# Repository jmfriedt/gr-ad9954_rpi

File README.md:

# gr-ad9954_rpi

Daughter board for the Raspberry Pi 3 or 4 fitted with an Analog Devices AD9954 Direct 
Digital Synthesizer.

KiCAD 6 schematic and board are provided.

Mechanical analysis using FreeCAD of the board compatibility with the RPi4:

The Python 3 script ``ad9954.py`` was used to demonstrate proper operation of the board:

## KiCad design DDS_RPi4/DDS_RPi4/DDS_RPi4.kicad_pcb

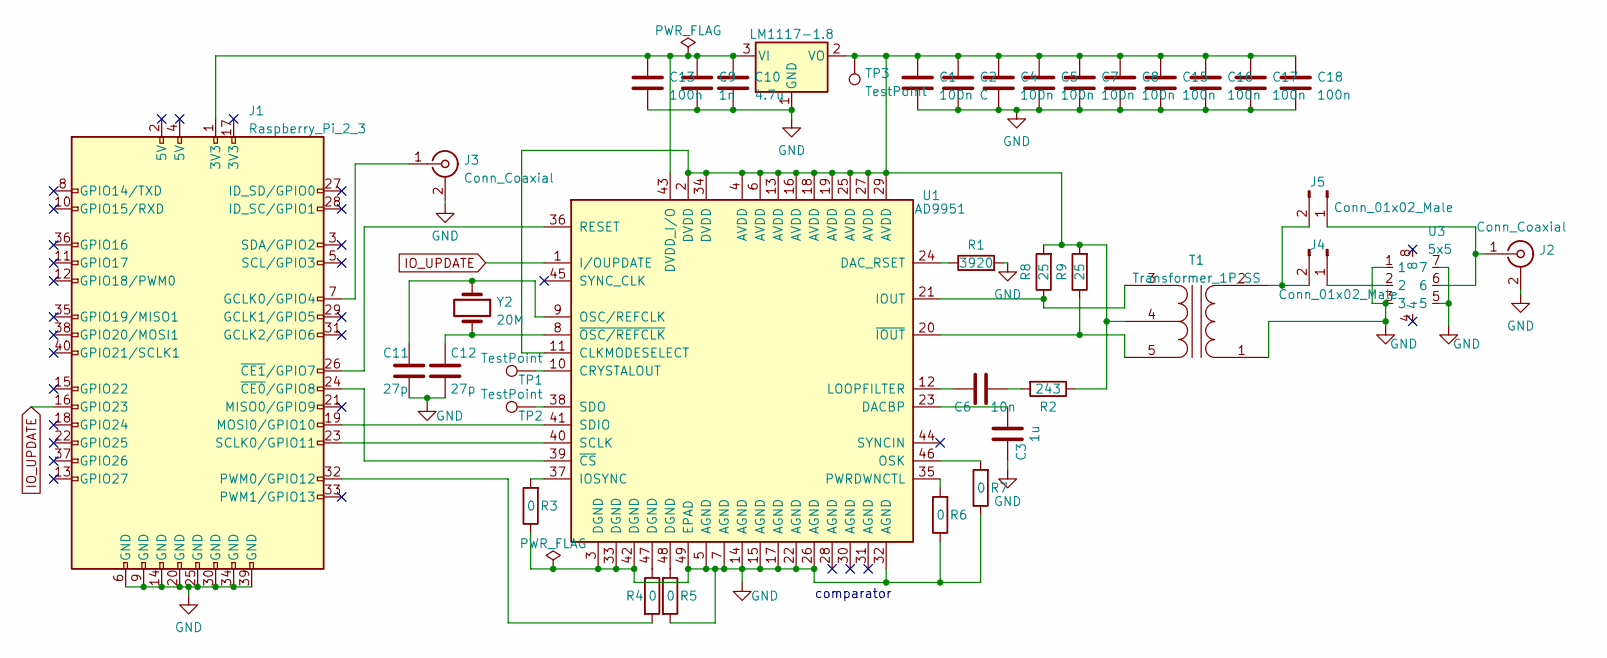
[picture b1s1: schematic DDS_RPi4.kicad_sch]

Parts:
C1, C4, C5, C7, C8, C13, C15, C16, C17, C18: 100n; C_0603_1608Metric_Pad1.08x0.95mm_HandSolder
C2: C; C_0603_1608Metric_Pad1.08x0.95mm_HandSolder
C3: 1u; C_0603_1608Metric_Pad1.08x0.95mm_HandSolder
C6: 10n; C_0603_1608Metric_Pad1.08x0.95mm_HandSolder
C9: 1n; C_0603_1608Metric_Pad1.08x0.95mm_HandSolder
C10: 4.7u; C_0603_1608Metric_Pad1.08x0.95mm_HandSolder
C11, C12: 27p; C_0603_1608Metric_Pad1.08x0.95mm_HandSolder
J1: Raspberry_Pi_2_3; PinSocket_2x20_P2.54mm_Vertical
J2, J3: Conn_Coaxial; SMA_Molex_73251-2120_EdgeMount_Horizontal
J4, J5: Conn_01x02_Male; PinHeader_1x02_P2.54mm_Vertical
R1: 3920; R_0603_1608Metric_Pad0.98x0.95mm_HandSolder
R2: 243; R_0603_1608Metric_Pad0.98x0.95mm_HandSolder
R3, R4, R5, R6, R7: 0; R_0603_1608Metric_Pad0.98x0.95mm_HandSolder
R8, R9: 25; R_0603_1608Metric_Pad0.98x0.95mm_HandSolder
T1: Transformer_1P_SS; Transformer_MACOM_SM-22
TP1, TP2, TP3: TestPoint; TestPoint_Pad_1.0x1.0mm
U1: AD9951; TQFP-48-1EP_7x7mm_P0.5mm_EP3.5x3.5mm
U2: LM1117-1.8; SOT-223-3_TabPin2
U3: 5x5
Y2: 20M; Crystal_SMD_HC49-SD_HandSoldering

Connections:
GND: C1.2, C2.2, C3.1, C4.2, C5.2, C7.2, C8.2, C9.2, C10.2, C11.2, C12.2, C13.2, C15.2, C16.2, C17.2, C18.2, J1.6 (GND), J1.9 (GND), J1.14 (GND), J1.20 (GND), J1.25 (GND), J1.30 (GND), J1.34 (GND), J1.39 (GND), J2.2 (Ext), J3.2 (Ext), R1.2, R3.1, R5.2, R6.1, R7.1, T1.1 (AA), U1.3 (DGND), U1.5 (AGND), U1.7 (AGND), U1.14 (AGND), U1.15 (AGND), U1.17 (AGND), U1.22 (AGND), U1.26 (AGND), U1.32 (AGND), U1.33 (DGND), U1.42 (DGND), U1.49 (EPAD), U2.1 (GND), U3.1, U3.3, U3.5, U3.7
IO_UPDATE: J1.16 (GPIO23), U1.1 (I/OUPDATE)
unnamed: C1.1, C2.1, C4.1, C5.1, C7.1, C8.1, C15.1, C16.1, C17.1, C18.1, R2.1, R8.2, R9.2, T1.4 (SC), TP3.1, U1.2 (DVDD), U1.4 (AVDD), U1.6 (AVDD), U1.11 (CLKMODESELECT), U1.13 (AVDD), U1.16 (AVDD), U1.18 (AVDD), U1.19 (AVDD), U1.25 (AVDD), U1.27 (AVDD), U1.29 (AVDD), U1.34 (DVDD), U2.2 (VO)
unnamed: C3.2, U1.23 (DACBP)
unnamed: C6.1, U1.12 (LOOPFILTER)
unnamed: C6.2, R2.2
unnamed: C9.1, C10.1, C13.1, J1.1 (3V3), U1.43 (DVDD_I/O), U2.3 (VI)
unnamed: C11.1, U1.9 (OSC/REFCLK), Y2.1
unnamed: C12.1, U1.8 (~OSC/REFCLK), Y2.2
unnamed: J1.7 (GCLK0/GPIO4), J3.1 (In)
unnamed: J1.19 (MOSI0/GPIO10), U1.41 (SDIO)
unnamed: J1.23 (SCLK0/GPIO11), U1.40 (SCLK)
unnamed: J1.24 (~CE0/GPIO8), U1.39 (~CS)
unnamed: J1.26 (~CE1/GPIO7), U1.36 (RESET)
unnamed: J1.32 (PWM0/GPIO12), R4.2
unnamed: J2.1 (In), J5.1, U3.6
unnamed: J4.1, U3.2
unnamed: J4.2, J5.2, T1.2 (AB)
unnamed: R1.1, U1.24 (DAC_RSET)
unnamed: R3.2, U1.37 (IOSYNC)
unnamed: R4.1, U1.47 (DGND)
unnamed: R5.1, U1.48 (DGND)
unnamed: R6.2, U1.35 (PWRDWNCTL)
unnamed: R7.2, U1.46 (OSK)
unnamed: R8.1, T1.3 (SA), U1.21 (IOUT)
unnamed: R9.1, T1.5 (SB), U1.20 (~IOUT)
unnamed: TP1.1, U1.10 (CRYSTALOUT)
unnamed: TP2.1, U1.38 (SDO)

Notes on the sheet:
comparator

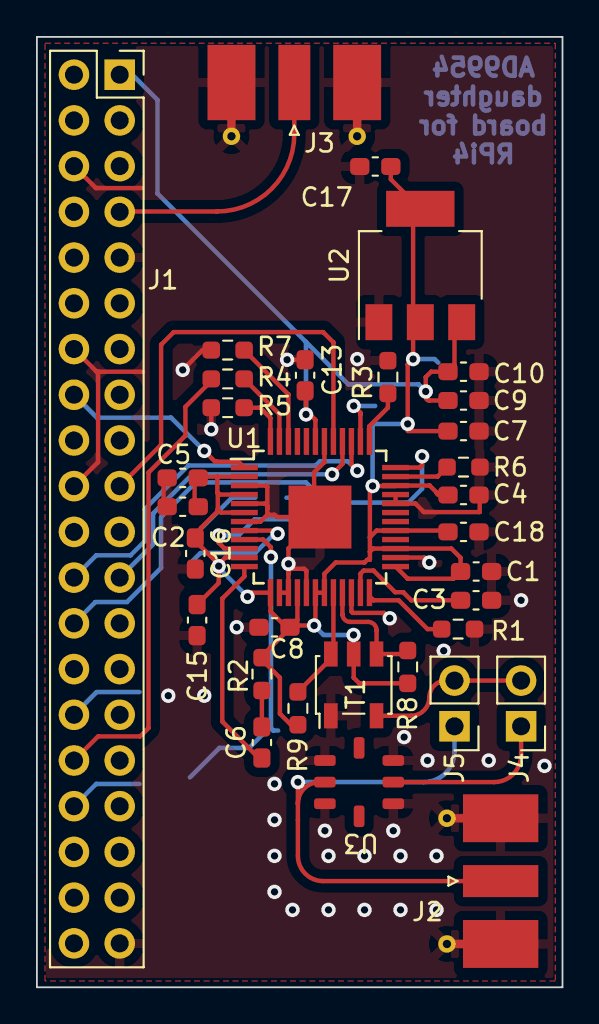
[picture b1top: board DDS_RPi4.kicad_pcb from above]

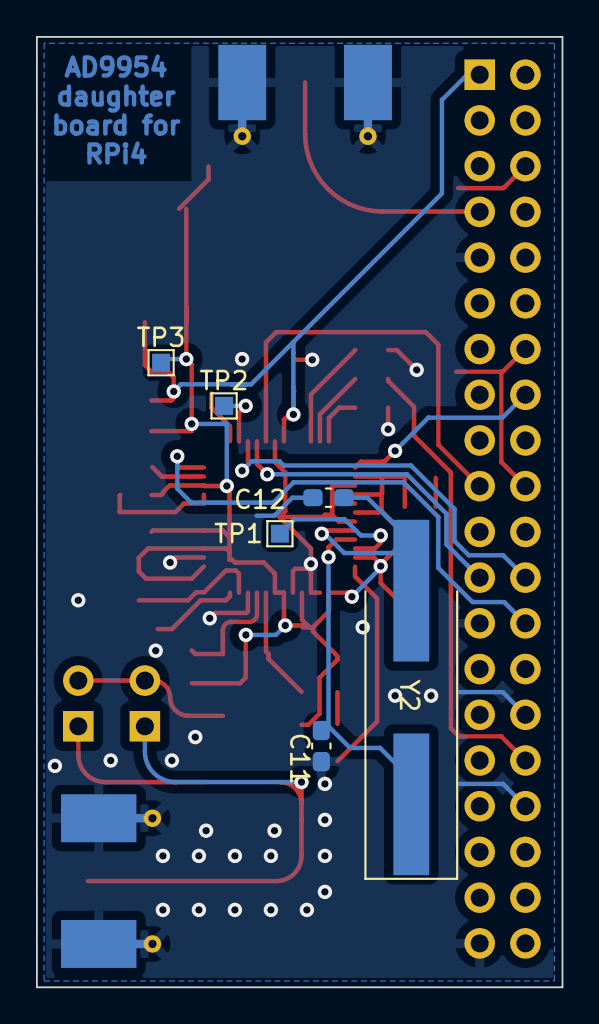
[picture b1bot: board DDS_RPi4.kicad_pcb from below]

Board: 2 copper layers, 29.2 x 52.8 mm, 39 parts (6 on the bottom side), 28 nets.

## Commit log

2023-02-21 update schematic and PCB (disconnect comparator out and add more decoupling capacitors)
